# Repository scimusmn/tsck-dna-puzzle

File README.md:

tsck-dna-puzzle
===============

This repository contains software and hardware files for the [DNA Puzzle for TSCK].

The puzzle consists of a steel double-helix with embedded RFID readers, individual
"nucleotide" pieces containing RFID tags, and a large stele containing an LED
disk that displays an "eye", whose appearance changes based on the arrangement
of nucleotides in the helix.

software
--------

The software is split into three pieces: 

* the RFID readers, which collect UART data from the reader modules and store it
  to be served via I2C (stored in `arduino/rfid-attiny`);
* the main controller, which reads the stored data on the RFID readers via I2C,
  updates the internal genome data, and then transmits it to the lighting controller
  (stored in `arduino/controller`); and
* the lighting controller, which received genome data from the main controller and 
  updates the LEDs as appropriate (stored in `arduino/lighting-controller`).

hardware
--------

There are two broad categories of hardware included in this repository:

* CAD files (mostly laser-cut pieces) stored in `laser-cutter`; and
* electronics (both schematics and PCB layouts) stored in `electronics`.

[DNA Puzzle for TSCK]: https://drive.google.com/drive/folders/1d9PLsUjKqNwdjKIzH2Ln1TuXTCMuD0Dc

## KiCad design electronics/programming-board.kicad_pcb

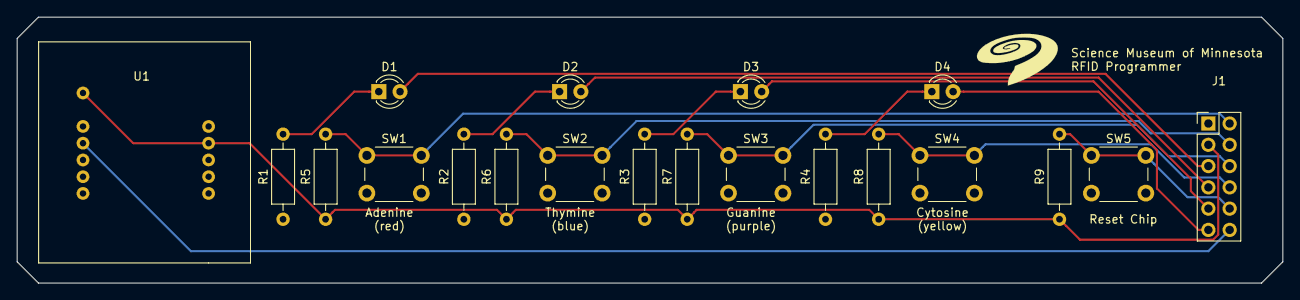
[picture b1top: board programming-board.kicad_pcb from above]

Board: 2 copper layers, 151.1 x 31.8 mm, 20 parts (0 on the bottom side), 16 nets.

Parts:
D1, D2, D3, D4: LED; LED_D3.0mm
J1: Conn_02x06_Odd_Even; PinHeader_2x06_P2.54mm_Vertical
R1, R2, R3, R4: 1k; R_Axial_DIN0207_L6.3mm_D2.5mm_P10.16mm_Horizontal
R5, R6, R7, R8, R9: 10k; R_Axial_DIN0207_L6.3mm_D2.5mm_P10.16mm_Horizontal
SW1, SW2, SW3, SW4, SW5: SW_Push; SW_PUSH_6mm_H4.3mm
U1: ID12-LA; ID-12LA

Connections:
+5V: J1.3, R5.1, R6.1, R7.1, R8.1, R9.1, U1.2, U1.11
/B1: J1.2, R5.2, SW1.1
/B2: J1.4, R6.2, SW2.1
/B3: J1.6, R7.2, SW3.1
/B4: J1.8, R8.2, SW4.1
/B5: J1.10, R9.2, SW5.1
/LED1: D1.2, J1.5
/LED2: D2.2, J1.7
/LED3: D3.2, J1.9
/LED4: D4.2, J1.11
GND: J1.1, R1.1, R2.1, R3.1, R4.1, SW1.2, SW2.2, SW3.2, SW4.2, SW5.2, U1.1, U1.7
unnamed: D1.1, R1.2
unnamed: D2.1, R2.2
unnamed: D3.1, R3.2
unnamed: D4.1, R4.2
unnamed: J1.12, U1.9

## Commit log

2021-05-26 add basic lighting sketch
2021-06-02 move to 18-segment genome output
2021-06-14 add rfid reader sketch
2021-09-28 add board templates and update lighting code
2021-11-03 begin test-driven lighting refactor
2021-11-03 update README.md and license file
2021-11-04 refactor: *.c -> *.cpp
2021-11-04 add tests for Ring class
2022-01-24 refactor: move all arduino code into arduino/ and rename appropriately
2022-01-24 add electronic hardware files
2022-01-24 move laser cut files into single folder
2022-01-24 rename: dna-puzzle-electronics -> electronics
2022-01-25 implement controller's programmer board
2022-02-14 update lighting
2022-02-14 add TimeoutTimer
2022-02-14 improve RFID reader sketch
2022-02-15 switch Reader sketch to unix line endings
2022-02-15 move controller/Rfid/Reader sketch over rfid-attiny
2022-02-15 add README.md and fix timing
2022-02-15 fix lighting clock/data pins
2022-05-20 fix undo failure
2022-07-21 add drive link in README.md
2022-07-25 add README.md
2022-07-25 comment ProgrammerLeds.h
2022-07-27 add 5-second reset
2022-07-27 clean temp files
